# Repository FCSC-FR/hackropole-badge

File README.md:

# Hackropole badge

<!--
SPDX-FileCopyrightText: 2025 Hackropole
SPDX-License-Identifier: CC-BY-4.0
-->

This repository contains the source files and build instructions for the
Hackropole badge.

See [./hardware/](./hardware/) for PCB source files, and production instructions.

See [./assembly/](./assembly/README.en.md) for PCB assembly instructions
(available [in French](./assembly/README.fr.md) and [in English](./assembly/README.en.md)).

See [./firmware-wled/](./firmware-wled/README.en.md) for firmware flashing and
configuration guide (available [in French](./firmware-wled/README.fr.md) and
[in English](./firmware-wled/README.en.md)).

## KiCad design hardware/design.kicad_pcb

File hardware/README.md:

# Hackropole badge

<!--
SPDX-FileCopyrightText: 2025 Hackropole
SPDX-License-Identifier: CC-BY-4.0
-->

This PCB was designed with Kicad 9.0.

## Sending the PCB to production

We recommend the following settings when sending the design files to production:

- FR-4 base material, 2 layers, 1.6mm thickness,
- Blue color (to match Hackropole colors!),
- Leadfree HASL surface finish, or ENIG (gold),
- If your fab requires to place a mark on the PCB, you may use
  "Specify Position" and update the "JLCJLCJLCJLC" text.

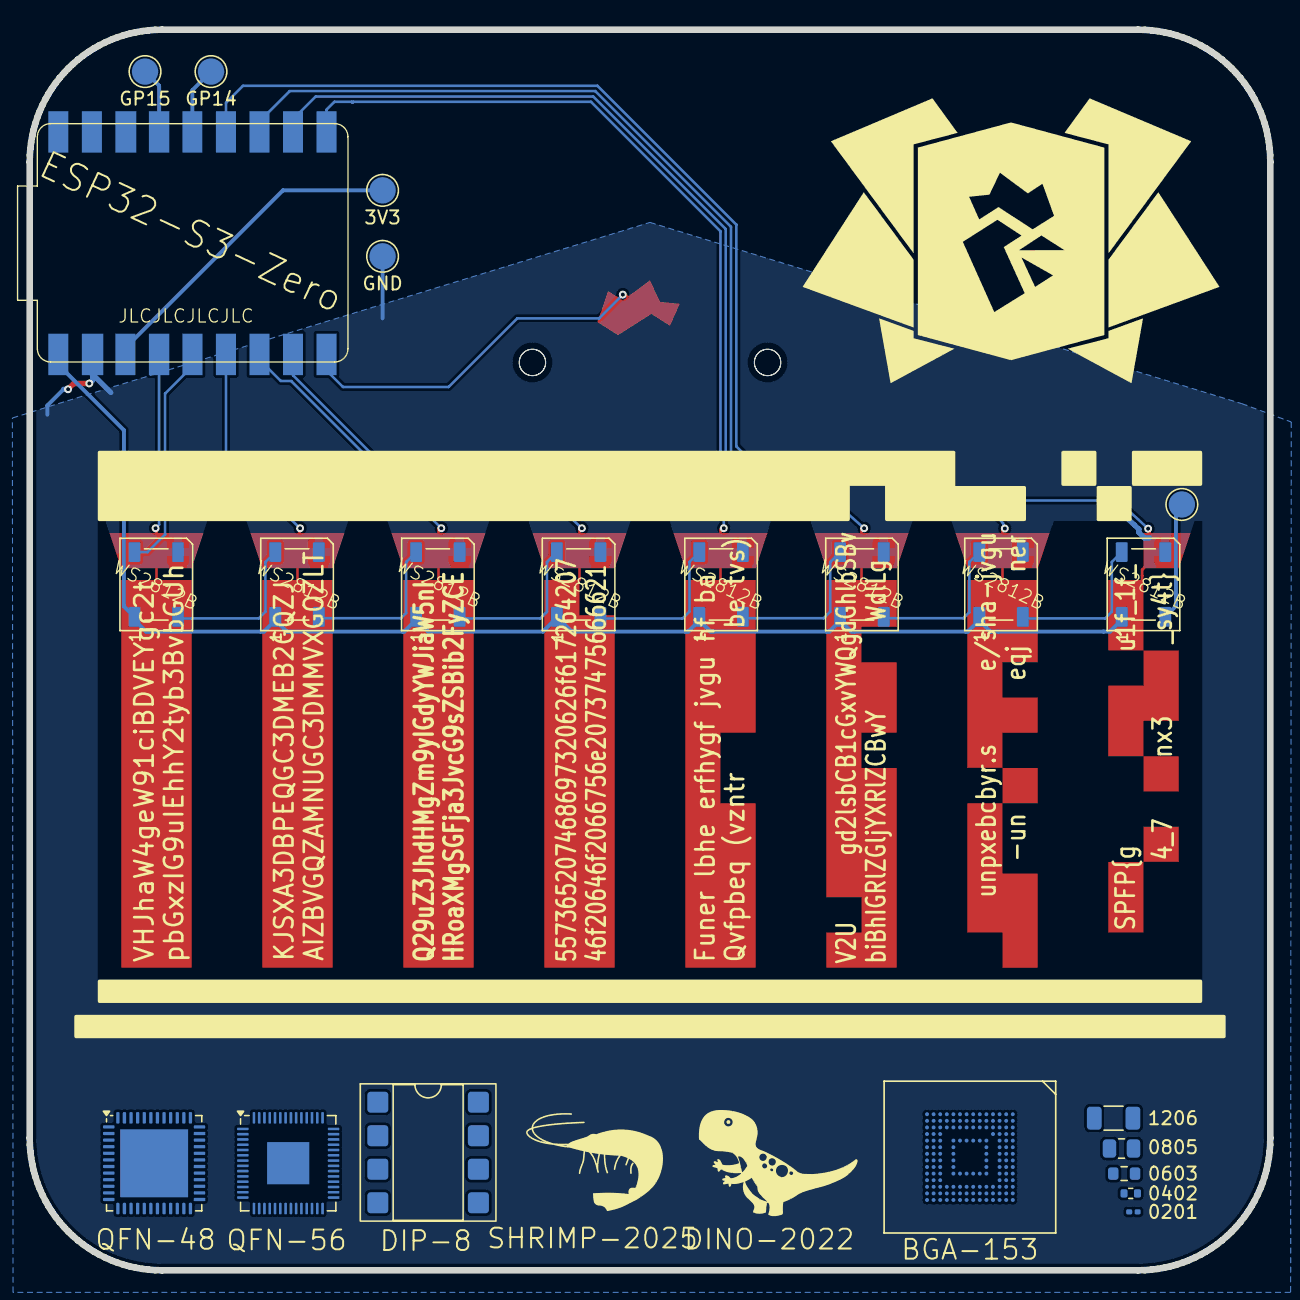
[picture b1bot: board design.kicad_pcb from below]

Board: 2 copper layers, 94.0 x 94.0 mm, 22 parts (22 on the bottom side), 14 nets.

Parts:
D1, D2, D3, D4, D5, D6, D7, D8: WS2812B; LED_WS2812B_PLCC4_5.0x5.0mm_P3.2mm
R1: 0201; R_0201_0603Metric
R2: 0402; R_0402_1005Metric
R3: 0603; R_0603_1608Metric
R4: 0805; R_0805_2012Metric
R5: 1206; R_1206_3216Metric
TP1: GP15; TestPoint_Pad_D2.0mm
TP2: GP14; TestPoint_Pad_D2.0mm
TP3: 3V3; TestPoint_Pad_D2.0mm
TP4: GND; TestPoint_Pad_D2.0mm
TP5: DOUT; TestPoint_Pad_D2.0mm
U1: ESP32-S3-Zero; Waveshare-ESP32-S3-Zero
U2: DIP-8; DIP-8_W7.62mm_SMDSocket_SmallPads
U3: RP2040; QFN-56-1EP_7x7mm_P0.4mm_EP3.2x3.2mm
U4: AMT49413; QFN-48-1EP_7x7mm_P0.5mm_EP5.15x5.15mm

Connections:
+3.3V: TP3.1, U1.3 (3V3(OUT))
+5V: D1.1 (VDD), D2.1 (VDD), D3.1 (VDD), D4.1 (VDD), D5.1 (VDD), D6.1 (VDD), D7.1 (VDD), D8.1 (VDD), U1.1 (VDD)
/GP14: TP2.1, U1.14 (GPIO11)
/GP15: TP1.1, U1.15 (GPIO12)
/LED_DIN: D1.4 (DIN), U1.5 (GPIO2)
/LED_DOUT: D8.2 (DOUT), TP5.1
GND: D1.3 (VSS), D2.3 (VSS), D3.3 (VSS), D4.3 (VSS), D5.3 (VSS), D6.3 (VSS), D7.3 (VSS), D8.3 (VSS), TP4.1, U1.2 (GND)
unnamed: D1.2 (DOUT), D2.4 (DIN)
unnamed: D2.2 (DOUT), D3.4 (DIN)
unnamed: D3.2 (DOUT), D4.4 (DIN)
unnamed: D4.2 (DOUT), D5.4 (DIN)
unnamed: D5.2 (DOUT), D6.4 (DIN)
unnamed: D6.2 (DOUT), D7.4 (DIN)
unnamed: D7.2 (DOUT), D8.4 (DIN)

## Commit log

2025-09-06 Add WLED screenshot
2025-09-06 Add picture
2025-09-06 Minor pcb changes
2025-09-06 Improve assembly instructions
2025-09-06 Add README
2025-09-06 Update assembly instructions
2025-09-06 Translation and formatting
2025-09-13 assembly: fix typo in README
